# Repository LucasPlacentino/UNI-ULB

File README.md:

# UNI-ULB_edu
Personal university files, documents and projects.  

### [Lucas Placentino](https://github.com/LucasPlacentino)  
**ULB - https://ulb.ac.be/en  
École Polytechnique de Bruxelles - https://polytech.ulb.be/en**  

## BA1
- ### <a href='BA1/INFOH100'><ins>↪️ Project cs : Informatique I</ins></a> - INFO-H100  
  Vasarely mathematical painting using turtle module, in Python  
- ### <a href='BA1/TRANH201'><ins>↪️ Project BA1 : Projet d'année</ins></a> - TRANH101  
  _**..---..TBA..---..**_  

## BA2
- ### <a href='BA2/INFOH2001'><ins>↪️ Project cs : Informatique II</ins></a> - INFO-H2001  
  > <i>https://github.com/lucasplacentino/App-BA2-Project-Ecommerce</i>
  
  E-Commerce app built in Kotlin for Android  
- ### <a href='BA2/TRANH201'><ins>↪️ Project BA2 : Projet d'année</ins></a> - TRAN-H201  
  > <i>https://github.com/lucasplacentino/TRANH201INFO3-Sequencer</i>
  
  Sequencer for analog modular synth, built with Python on a RaspberryPi 3  
- ### <a href='BA2/ANANUM'><ins>↪️ Course : Analyse Numérique</ins></a> - MATH-H202  
  > <i>http://metronu.ulb.ac.be/MATH-H-202/</i>
  
  Octave (Matlab)  
  
## BA3
- ### <a href='BA3/TRANH3001'><ins>↪️ Course : Épistémologie des sciences et Éthique de l'ingénieur</ins></a> - TRANH3001  
  (Notes .md)  
- ### <a href='BA3/ELEC-H305'><ins>↪️ Course : Circuits logiques et numériques</ins></a> - ELEC-H305  
  Also C programming language (.c files, etc)
- ### <a href='https://github.com/DemonicTricycle/DemonicTricycle-ELECH309'><ins>↪️ Project BA3: Projet Intégré</ins></a> - ELEC-H309  
  #### "Demonic Tricycle"
  > <i>and https://github.com/lucasplacentino/Project-ELECH309.X for some tests</i>
- ### <a href="https://github.com/LucasPlacentino/UNI-ULB/tree/main/BA3/MECA-H301"><ins>↪️ Course: Thermodynamique Appliquée/Systèmes énergétiques : principes de bases et technologies durables</ins></a> - MECA-H301  
  (Notes .md)  
- ### <a href="https://github.com/LucasPlacentino/UNI-ULB/tree/main/BA3/MECA-H3001"><ins>↪️ Course: Fluid Mechanics and Transfer Processes</ins></a> - MECA-H3001
  (Notes .md)  
  
## MA1
- ### <a href='MA1/ELEC-H409%20Digital%20Architectures%20%26%20Design'><ins>↪️ Course : Digital Architectures & Design</ins></a> - ELEC-H409  
  (Notes .md)

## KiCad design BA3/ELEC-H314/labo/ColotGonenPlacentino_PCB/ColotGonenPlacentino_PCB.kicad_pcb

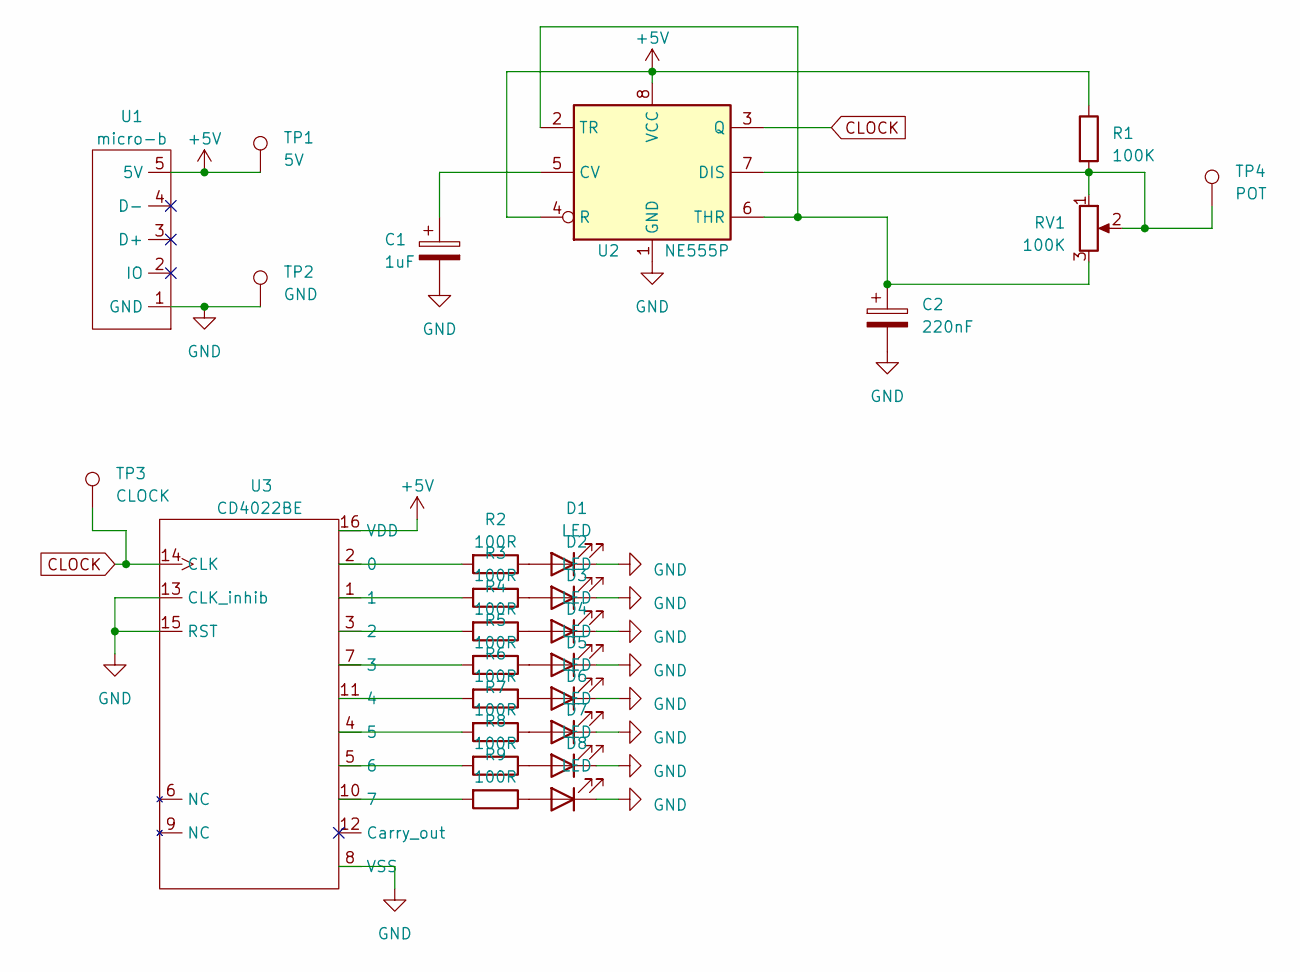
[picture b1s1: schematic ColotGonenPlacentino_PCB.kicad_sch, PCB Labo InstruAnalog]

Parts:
C1: 1uF; CP_Radial_D5.0mm_P2.00mm
C2: 220nF; CP_Radial_D5.0mm_P2.00mm
D1, D2, D3, D4, D5, D6, D7, D8: LED; LED_D5.0mm
R1: 100K; R_Axial_DIN0207_L6.3mm_D2.5mm_P7.62mm_Horizontal
R2, R3, R4, R5, R6, R7, R8, R9: 100R; R_Axial_DIN0414_L11.9mm_D4.5mm_P15.24mm_Horizontal
RV1: 100K; Potentiometer_Bourns_PTV09A-1_Single_Vertical
TP1: 5V; TestPoint_Pad_D1.5mm
TP2: GND; TestPoint_Pad_D1.5mm
TP3: CLOCK; TestPoint_Pad_D1.5mm
TP4: POT; TestPoint_Pad_D1.5mm
U1: micro-b; micro-b_adafruit
U2: NE555P; DIP-8_W7.62mm
U3: CD4022BE; DIP-16_W7.62mm

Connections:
+5V: R1.1, TP1.1, U1.5 (5V), U2.4 (R), U2.8 (VCC), U3.16 (VDD)
CLOCK: TP3.1, U2.3 (Q), U3.14 (CLK)
GND: C1.2, C2.2, D1.1 (K), D2.1 (K), D3.1 (K), D4.1 (K), D5.1 (K), D6.1 (K), D7.1 (K), D8.1 (K), TP2.1, U1.1 (GND), U2.1 (GND), U3.8 (VSS), U3.13 (CLK_inhib), U3.15 (RST)
unnamed: D1.2 (A), R2.1
unnamed: D2.2 (A), R3.1
unnamed: D3.2 (A), R4.1
unnamed: D4.2 (A), R5.1
unnamed: D5.2 (A), R6.1
unnamed: D6.2 (A), R7.1
unnamed: D7.2 (A), R8.1
unnamed: D8.2 (A), R9.1
unnamed: R3.2, U3.1
unnamed: C1.1, U2.5 (CV)
unnamed: R1.2, RV1.1, RV1.2, TP4.1, U2.7 (DIS)
unnamed: C2.1, RV1.3, U2.2 (TR), U2.6 (THR)
unnamed: R2.2, U3.2 (0)
unnamed: R4.2, U3.3 (2)
unnamed: R5.2, U3.7 (3)
unnamed: R6.2, U3.11 (4)
unnamed: R7.2, U3.4 (5)
unnamed: R8.2, U3.5 (6)
unnamed: R9.2, U3.10 (7)

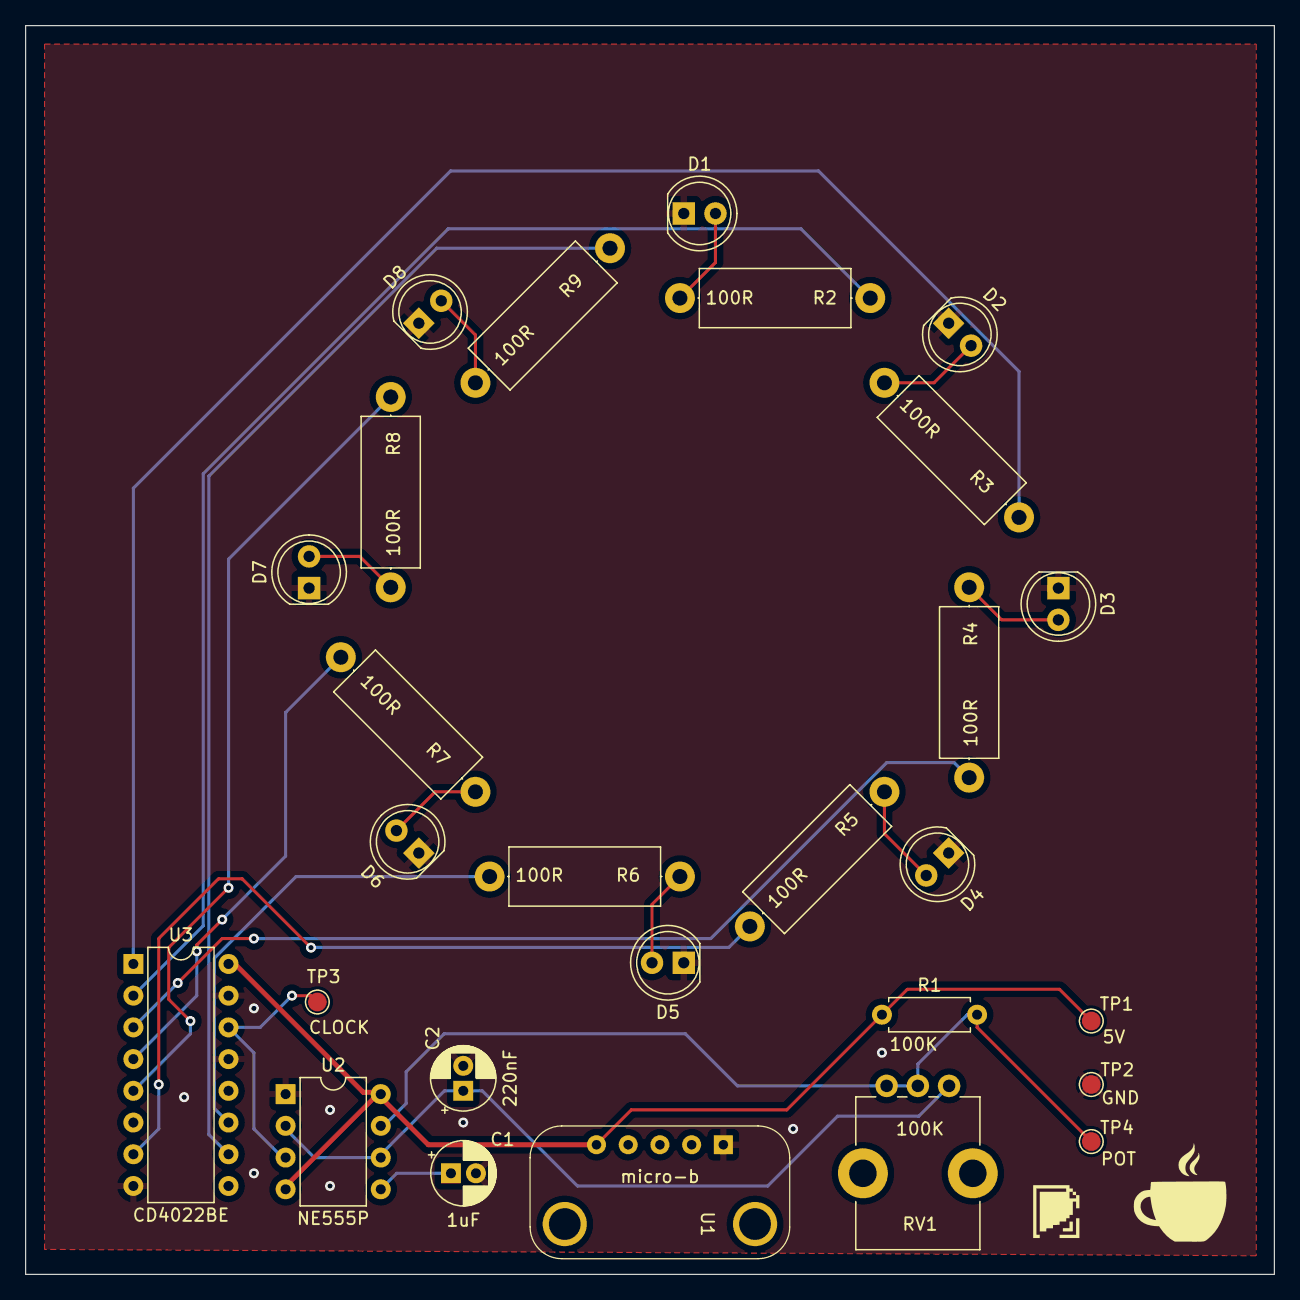
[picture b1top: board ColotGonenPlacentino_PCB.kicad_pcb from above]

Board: 2 copper layers, 100.0 x 100.0 mm, 27 parts (0 on the bottom side), 22 nets.

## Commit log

2021-08-17 added vasarely folder and readme
2021-08-17 added Vasarely project
2021-08-17 Rename Vasarely_ulb-h-lplacent/README.md to BA1/INFOH100/Vasarely_ulb-h-lplacent/README.md
2021-08-17 vasarely project
2021-08-17 added INFO-H2001
2021-08-17 added files
2022-02-20 moved files
2022-02-20 added all local files from main desktop pc
2022-02-20 GET and Release apk
    v1
2022-02-20 Rename main.yml to get-apk-an-release-it-here.yml
2022-02-20 test
2022-02-20 Update get-apk-an-release-it-here.yml
    v2
2022-02-20 Update get-apk-an-release-it-here.yml
    added auto release from other repo
2022-02-20 renamed directory tranh201
    removed hyphen
2022-04-22 added ananum files
2022-04-22 tp8 Newton-Raphson changé pour vectoriel
    marche aussi en scalaire
2022-05-06 tp10
    pas fait l'ex 2 et 3
2022-05-13 tp11
2022-05-20 tp12
2022-06-02 created tranh3001 folder
2022-06-02 added notes epistemo et ethique
2022-06-06 fixed tranh3001 to ba3
2022-06-06 fix : moved tranh3001 to ba3
2022-10-14 add elec-h305 and Obsidian config
2022-10-23 ignore .exe
2022-10-23 Q10 arrays
2023-02-24 fix ||^x - x|| / ||x|| comparaison à l'err relative
2023-04-19 fix ananaum
2023-05-23 Rename entrainement2ndesession.m to Entrainement2ndeSession2022.m
2023-06-09 add ananum files et synthese
2023-08-03 add examens ananum juin 22-23
2023-08-03 add exams ananum 2eme session 19 et 22
2023-08-03 Update ananum23.md
    replace `\^` with `\hat{}` because of mathjax outside github's md viewer
2023-08-03 Update ananum23.md
    replace `\~{}` to `\widetilde{}` and `\hat{}` to `\widehat{}` (for mathjax)
2023-08-03 update synthese ananum23
2023-08-03 ananum: ajout résolution et coût QR
2023-08-03 try github flavored markdown alerts
2023-08-03 ananum: ajout résolution et coût PALU
2023-08-04 ananum: fix Trapèzes, Simpson et Newton-Cotes
2023-08-04 ananum: fix typos
2023-08-04 ananum: fix floating point
2023-08-04 ananum: add examples floating point
2023-08-04 ananum: add calcul du dét de A avec PALU
2023-08-04 ananum: add inversion avec PALU
2023-08-14 ananum: fix tilde
2023-08-14 test pages ananum
2023-08-15 ananum: typo
2023-08-15 ananum: entrainement
2023-08-15 ananum: update
2023-09-20 add notes mecaflotte
2023-09-26 add figures thermo appl
2023-09-28 add cours 3 Signaux & Systèmes
2023-10-08 [ImgBot] Optimize images
    *Total -- 10,777.43kb -> 6,736.46kb (37.49%)
    /BA2/TRANH201/InkedCRAVE_use_LI.jpg -- 2,618.60kb -> 607.10kb (76.82%)
    /BA2/INFOH2001/ClassDiagram.png -- 257.80kb -> 118.13kb (54.18%)
    /BA2/INFOH2001/SequenceDiagram.png -- 258.26kb -> 122.88kb (52.42%)
    /BA2/TRANH201/Sequencer Design rev2.1.png -- 75.54kb -> 40.18kb (46.81%)
    /BA2/TRANH201/Sequencer Design rev2.0.png -- 73.93kb -> 39.40kb (46.71%)
2023-10-19 add signaux systemes cours Y
2024-05-02 phystel
2024-05-17 [ImgBot] Optimize images
    *Total -- 45,509.95kb -> 37,523.98kb (17.55%)
    /BA2/TRANH201/InkedCRAVE_use_LI.jpg -- 2,618.60kb -> 607.10kb (76.82%)
    /BA3/MATH-H304/labo7/bode1.png -- 75.91kb -> 28.82kb (62.03%)
    /BA3/ELEC-H314/labo/Labo2/LAbo2/Labo 2 - Filtres analogiques et transformation bilinéaire-20240419/image-13.png -- 6.52kb -> 2.61kb (60%)
    /BA3/MATH-H304/labo7/wut-discretise-bode.png -- 40.14kb -> 16.49kb (58.92%)
    /BA3/ELEC-H304/image-54.png -- 20.46kb -> 9.02kb (55.9%)
2024-06-07 upload files
2024-06-11 ananum juin 2024
2024-06-12 ananum24
2024-06-12 yep ananum
2024-07-30 cf pages instead of gh pages
2025-04-18 update phystel
2025-09-24 digital arch lectures
2025-09-24 [ImgBot] Optimize images
    *Total -- 46,661.36kb -> 38,365.85kb (17.78%)
    /BA2/TRANH201/InkedCRAVE_use_LI.jpg -- 2,618.60kb -> 607.10kb (76.82%)
    /BA3/MATH-H304/labo7/bode1.png -- 75.91kb -> 28.82kb (62.03%)
    /BA3/ELEC-H314/labo/Labo2/LAbo2/Labo 2 - Filtres analogiques et transformation bilinéaire-20240419/image-13.png -- 6.52kb -> 2.61kb (60%)
    /BA3/MATH-H304/labo7/wut-discretise-bode.png -- 40.14kb -> 16.49kb (58.92%)
    /BA3/ELEC-H304/image-54.png -- 20.46kb -> 9.02kb (55.9%)
2025-10-01 Upgrade artifacts GitHub Actions to latest versions
2025-10-01 Update course links and descriptions in README
2025-11-05 DSP Lab 1
2026-03-05 uC lab 1
2026-03-06 MDDM lab 1
2026-03-11 lab 2 µC
2026-03-23 Image Processing lab 1
2026-03-26 µC lab 3 (keypad)
